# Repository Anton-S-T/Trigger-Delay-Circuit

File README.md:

# Trigger-Delay-Circuit
A circuit to delay a rising edge or the falling edge of a trigger signal.

The board is a four layer board.

Layout:

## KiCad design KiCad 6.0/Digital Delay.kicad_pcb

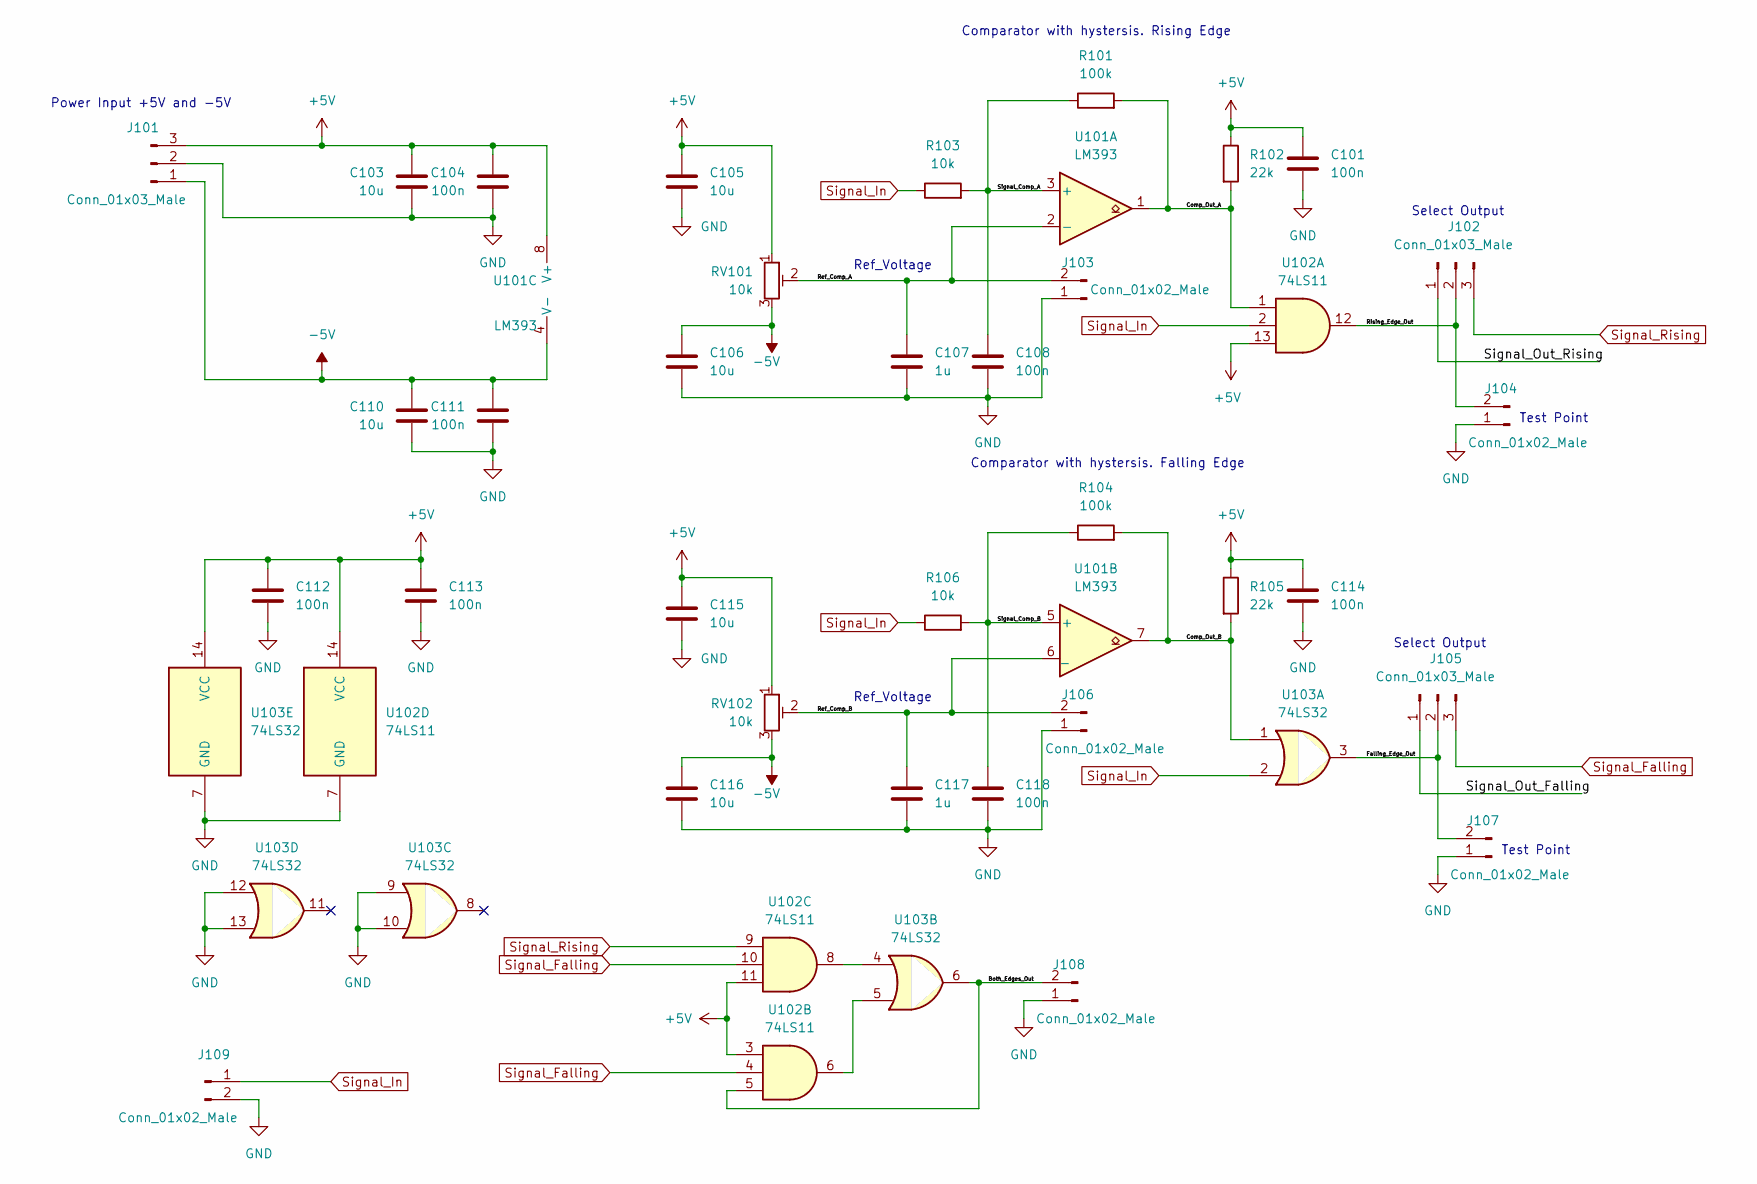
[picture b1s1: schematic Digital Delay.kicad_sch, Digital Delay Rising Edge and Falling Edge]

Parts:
C101, C104, C108, C111, C112, C113, C114, C118: 100n; C_0805_2012Metric
C103, C105, C106, C110, C115, C116: 10u; C_0805_2012Metric
C107, C117: 1u; C_0805_2012Metric
J101, J102, J105: Conn_01x03_Male; PinHeader_1x03_P2.54mm_Vertical
J103, J104, J106, J107, J108, J109: Conn_01x02_Male; PinHeader_1x02_P2.54mm_Vertical
R101, R104: 100k; C_0805_2012Metric
R102, R105: 22k; C_0805_2012Metric
R103, R106: 10k; C_0805_2012Metric
RV101, RV102: 10k; Potentiometer_Bourns_3296W_Vertical
U101: LM393; SOIC-8_3.9x4.9mm_P1.27mm
U102: 74LS11; SOIC-14_3.9x8.7mm_P1.27mm
U103: 74LS32; SOIC-14_3.9x8.7mm_P1.27mm

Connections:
+5V: C101.1, C103.1, C104.1, C105.1, C112.1, C113.1, C114.1, C115.1, J101.3, R102.1, R105.1, RV101.1, RV102.1, U101.8 (V+), U102.3, U102.11, U102.13, U102.14 (VCC), U103.14 (VCC)
-5V: C106.1, C110.1, C111.1, C116.1, J101.1, RV101.3, RV102.3, U101.4 (V-)
/Both_Edges_Out: J108.2, U102.5, U103.6
/Comp_Out_A: R101.2, R102.2, U101.1, U102.1
/Comp_Out_B: R104.2, R105.2, U101.7, U103.1
/Falling_Edge_Out: J105.2, J107.2, U103.3
/Ref_Comp_A: C107.1, J103.2, RV101.2, U101.2 (-)
/Ref_Comp_B: C117.1, J106.2, RV102.2, U101.6 (_)
/Rising_Edge_Out: J102.2, J104.2, U102.12
/Signal_Comp_A: C108.1, R101.1, R103.2, U101.3 (+)
/Signal_Comp_B: C118.1, R104.1, R106.2, U101.5 (+)
/Signal_Out_Falling: J105.1
/Signal_Out_Rising: J102.1
GND: C101.2, C103.2, C104.2, C105.2, C106.2, C107.2, C108.2, C110.2, C111.2, C112.2, C113.2, C114.2, C115.2, C116.2, C117.2, C118.2, J101.2, J103.1, J104.1, J106.1, J107.1, J108.1, J109.2, U102.7 (GND), U103.7 (GND), U103.9, U103.10, U103.12, U103.13
unnamed: U102.6, U103.5
unnamed: U102.8, U103.4
Signal_Falling: J105.3, U102.4, U102.10
Signal_In: J109.1, R103.1, R106.1, U102.2, U103.2
Signal_Rising: J102.3, U102.9

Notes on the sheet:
Test Point
Power Input +5V and -5V
Ref_Voltage
Select Output
Comparator with hystersis. Falling Edge
Comparator with hystersis. Rising Edge

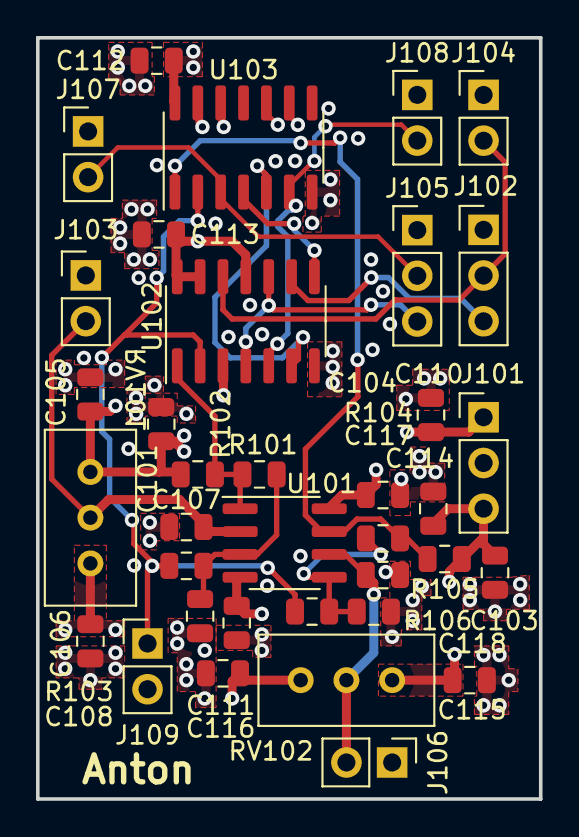
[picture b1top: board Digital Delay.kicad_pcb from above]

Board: 4 copper layers, 27.9 x 42.3 mm, 36 parts (0 on the bottom side), 17 nets.

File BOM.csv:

"Source:","C:\Users\NepToast\Desktop\Electronic Projects\digital delay\Digital Delay\Digital Delay.kicad_sch"
"Date:","15.10.2022 17:39:01"
"Tool:","Eeschema (6.0.8)"
"Generator:","C:\Program Files\KiCad\6.0\bin\scripting\plugins/bom_csv_grouped_by_value.py"
"Component Count:","36"

"Individual Components:"

"Item","Qty","Reference(s)","Value","LibPart","Footprint","Datasheet"
"","","C101","100n","Device:C","Capacitor_SMD:C_0805_2012Metric","~"
"","","C103","10u","Device:C","Capacitor_SMD:C_0805_2012Metric","~"
"","","C104","100n","Device:C","Capacitor_SMD:C_0805_2012Metric","~"
"","","C105","10u","Device:C","Capacitor_SMD:C_0805_2012Metric","~"
"","","C106","10u","Device:C","Capacitor_SMD:C_0805_2012Metric","~"
"","","C107","1u","Device:C","Capacitor_SMD:C_0805_2012Metric","~"
"","","C108","1n","Device:C","Capacitor_SMD:C_0805_2012Metric","~"
"","","C110","10u","Device:C","Capacitor_SMD:C_0805_2012Metric","~"
"","","C111","100n","Device:C","Capacitor_SMD:C_0805_2012Metric","~"
"","","C112","100n","Device:C","Capacitor_SMD:C_0805_2012Metric","~"
"","","C113","100n","Device:C","Capacitor_SMD:C_0805_2012Metric","~"
"","","C114","100n","Device:C","Capacitor_SMD:C_0805_2012Metric","~"
"","","C115","10u","Device:C","Capacitor_SMD:C_0805_2012Metric","~"
"","","C116","10u","Device:C","Capacitor_SMD:C_0805_2012Metric","~"
"","","C117","1u","Device:C","Capacitor_SMD:C_0805_2012Metric","~"
"","","C118","1n","Device:C","Capacitor_SMD:C_0805_2012Metric","~"
"","","J101","Conn_01x03_Male","Connector:Conn_01x03_Male","Connector_PinHeader_2.54mm:PinHeader_1x03_P2.54mm_Vertical","~"
"","","J102","Conn_01x03_Male","Connector:Conn_01x03_Male","Connector_PinHeader_2.54mm:PinHeader_1x03_P2.54mm_Vertical","~"
"","","J103","Conn_01x02_Male","Connector:Conn_01x02_Male","Connector_PinHeader_2.54mm:PinHeader_1x02_P2.54mm_Vertical","~"
"","","J104","Conn_01x02_Male","Connector:Conn_01x02_Male","Connector_PinHeader_2.54mm:PinHeader_1x02_P2.54mm_Vertical","~"
"","","J105","Conn_01x03_Male","Connector:Conn_01x03_Male","Connector_PinHeader_2.54mm:PinHeader_1x03_P2.54mm_Vertical","~"
"","","J106","Conn_01x02_Male","Connector:Conn_01x02_Male","Connector_PinHeader_2.54mm:PinHeader_1x02_P2.54mm_Vertical","~"
"","","J107","Conn_01x02_Male","Connector:Conn_01x02_Male","Connector_PinHeader_2.54mm:PinHeader_1x02_P2.54mm_Vertical","~"
"","","J108","Conn_01x02_Male","Connector:Conn_01x02_Male","Connector_PinHeader_2.54mm:PinHeader_1x02_P2.54mm_Vertical","~"
"","","J109","Conn_01x02_Male","Connector:Conn_01x02_Male","Connector_PinHeader_2.54mm:PinHeader_1x02_P2.54mm_Vertical","~"
"","","R101","100k","Device:R","Capacitor_SMD:C_0805_2012Metric","~"
"","","R102","22k","Device:R","Capacitor_SMD:C_0805_2012Metric","~"
"","","R103","10k","Device:R","Capacitor_SMD:C_0805_2012Metric","~"
"","","R104","100k","Device:R","Capacitor_SMD:C_0805_2012Metric","~"
"","","R105","22k","Device:R","Capacitor_SMD:C_0805_2012Metric","~"
"","","R106","10k","Device:R","Capacitor_SMD:C_0805_2012Metric","~"
"","","RV101","10k","Device:R_Potentiometer_Trim","Potentiometer_THT:Potentiometer_Bourns_3296W_Vertical","~"
"","","RV102","10k","Device:R_Potentiometer_Trim","Potentiometer_THT:Potentiometer_Bourns_3296W_Vertical","~"
"","","U101","LM393","Comparator:LM393","Package_SO:SOIC-8_3.9x4.9mm_P1.27mm","http://www.ti.com/lit/ds/symlink/lm393.pdf"
"","","U102","74LS11","74xx:74LS11","Package_SO:SOIC-14_3.9x8.7mm_P1.27mm","http://www.ti.com/lit/gpn/sn74LS11"
"","","U103","74LS32","74xx:74LS32","Package_SO:SOIC-14_3.9x8.7mm_P1.27mm","http://www.ti.com/lit/gpn/sn74LS32"



"Collated Components:"

"Item","Qty","Reference(s)","Value","LibPart","Footprint","Datasheet"
"1","6","C101, C104, C111, C112, C113, C114","100n","Device:C","Capacitor_SMD:C_0805_2012Metric","~"
"2","6","C103, C105, C106, C110, C115, C116","10u","Device:C","Capacitor_SMD:C_0805_2012Metric","~"
"3","2","C107, C117","1u","Device:C","Capacitor_SMD:C_0805_2012Metric","~"
"4","2","C108, C118","1n","Device:C","Capacitor_SMD:C_0805_2012Metric","~"
"5","3","J101, J102, J105","Conn_01x03_Male","Connector:Conn_01x03_Male","Connector_PinHeader_2.54mm:PinHeader_1x03_P2.54mm_Vertical","~"
"6","6","J103, J104, J106, J107, J108, J109","Conn_01x02_Male","Connector:Conn_01x02_Male","Connector_PinHeader_2.54mm:PinHeader_1x02_P2.54mm_Vertical","~"
"7","2","R101, R104","100k","Device:R","Capacitor_SMD:C_0805_2012Metric","~"
"8","2","R102, R105","22k","Device:R","Capacitor_SMD:C_0805_2012Metric","~"
"9","2","R103, R106","10k","Device:R","Capacitor_SMD:C_0805_2012Metric","~"
"10","2","RV101, RV102","10k","Device:R_Potentiometer_Trim","Potentiometer_THT:Potentiometer_Bourns_3296W_Vertical","~"
"11","1","U101","LM393","Comparator:LM393","Package_SO:SOIC-8_3.9x4.9mm_P1.27mm","http://www.ti.com/lit/ds/symlink/lm393.pdf"
"12","1","U102","74LS11","74xx:74LS11","Package_SO:SOIC-14_3.9x8.7mm_P1.27mm","http://www.ti.com/lit/gpn/sn74LS11"
"13","1","U103","74LS32","74xx:74LS32","Package_SO:SOIC-14_3.9x8.7mm_P1.27mm","http://www.ti.com/lit/gpn/sn74LS32"

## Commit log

2022-10-15 Create Description
2022-10-15 Update Description
